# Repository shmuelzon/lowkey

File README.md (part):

# LowKey

A battery-powered smart lock controller for a motorised deadbolt, built on the
Nordic **nRF54L15** with the nRF Connect SDK.

It speaks **Matter over Thread** and a **custom BLE GATT service at the same
time**, on one Bluetooth controller. The two are not alternatives selected at
build time - they run concurrently, each with its own advertising set and its
own Bluetooth identity, so the lock stays controllable over BLE when the Thread
mesh or the Matter controller is down, and its BLE bonds survive Matter
commissioning and Matter factory resets.

| On the bench | Installed in a door |
| --- | --- |
|  |  |

## Features

- **Three distinct actions**, matching what a mortise deadbolt can actually do:
  lock, unbolt (retract the bolt, spring latch still holds the door), and open
  (retract the bolt *and* hold the latch back so the door can be pushed).
  These map to the Matter `LockDoor`, `UnboltDoor` and `UnlockDoor` commands.
- **Position tracked from the bolt, not from the motor.** The lock body's two
  magnetic end-stop sensors are monitored continuously, so operating the lock
  with a physical key updates the reported state exactly like a remote command
  does.
- **Jam detection** - the motor stops and the lock reports jammed, with a Matter
  `DoorLockAlarm` event, if an end-stop is not reached in time.
- **Door position sensor**, reported as a Matter `DoorStateChange`.
- **Battery monitoring** with a MAX17205 ModelGauge m5 fuel gauge, plus charger
  connected/complete status.
- **Firmware update** over both Bluetooth SMP (MCUmgr) and Matter OTA, sharing
  one MCUboot slot pair with LZMA-compressed images.
- **Per-device provisioning** - serial number, BLE pairing passkey, Matter
  discriminator and SPAKE2+ verifier in a dedicated flash partition that OTA
  never touches.
- **Task watchdog** with a channel per critical thread.

## Hardware

### Lock body

The mechanism is a **Rav Bariach RBM1**, a motorised mortise lock. The motor
unit and the magnetic sensors for the two bolt end-stops come built into the
body. The controller only has to drive the motor and read the sensors, all
through one 6-pin harness:

| Pin | Signal |
| --- | --- |
| 1 | 3.3 V (sensor supply) |
| 2 | GND |
| 3 | Unlocked end-stop |
| 4 | Locked end-stop |
| 5, 6 | Motor |

See [Adapting to a different lock body](#adapting-to-a-different-lock-body) if
yours is different.

<br clear="right">

### Electronics

One KiCad project holds three boards, panelised with mouse bites:

- **Main board**: the **Ezurio BL54L15** module (nRF54L15, with an MHF4
  connector for an external antenna, so there is no RF switch to manage),
  charger, regulator, fuel gauge, motor driver, and connectors for the
  battery, the lock harness, the door sensor and SWD.
- **UI board**: the two keys, the status LED and the USB-C charging port. It
  connects to the main board over an 8-way FFC.
- **Door sensor board**: a single Hall sensor with a 3-pin JST XH cable to
  the main board. It also carries an alternative footprint for a Coto RR123
  magnetoresistive sensor, which is not fitted.

Power comes from a 2S Li-ion pack, two 18650 or 21700 cells in series, on a
2-pin JST XH connector. See [Battery life](#battery-life) for what to expect
from each.

| Part | Role |
| --- | --- |
| Ezurio 453-00044R (BL54L15) | nRF54L15 module |
| TE 2344656-6 | External 2.4 GHz antenna |
| TI BQ25886 | 2S battery charger from USB-C, 1.03 A charge current (ITERM 103 mA) |
| TI TPS629203 | 3.3 V buck regulator |
| ADI MAX17205 | 2S fuel gauge, I²C `0x36`, 10 mΩ shunt |
| TI DRV8871 | H-bridge motor driver |
| Honeywell SL353LT | Door sensor, on its own board |

- [**Schematic (PDF)**](hardware/pcb/smart-lock.pdf)
- [KiCad project](hardware/pcb/) (KiCad 10). Custom 3D models are embedded
  in the board file, so the 3D viewer needs no extra libraries.

### Enclosures

| Controller | UI |
| --- | --- |
|  |  |
| [`controller.stl`](hardware/3d/controller.stl), from [`controller.scad`](hardware/3d/controller.scad) | [`ui.stl`](hardware/3d/ui.stl), from [`ui.scad`](hardware/3d/ui.scad) |

- **Controller**: a 42 × 42 × 13.8 mm box for the main board. It has openings
  for the lock harness, the battery lead and the UI cable, and closes with
  three M2 countersunk screws into heat-set inserts.
- **UI**: a Ø34 mm dome for the UI board, with lock and unlock icons embossed
  beside the two key caps. It closes with two M2 countersunk screws into
  heat-set inserts.

Both enclosures use 3.45 mm outer-diameter M2 inserts. Each STL holds every
part of its enclosure (base, lid and, for the UI, the key caps) as separate
bodies; split them into objects in your slicer. The `show_*` variables at the
top of each `.scad` export a single part.

### Regenerating the outputs

The PDF, the renders and the STLs are committed so they can be viewed on
GitHub. After changing a source, regenerate them with:

```sh
make -C hardware          # everything
make -C hardware pcb      # schematic PDF and board render (KiCad 10)
make -C hardware 3d       # STLs and enclosure renders (OpenSCAD)
```

The Makefile finds `kicad-cli`, `openscad` and ImageMagick's `magick` in
`PATH`, in their usual macOS locations, and under `C:\Program Files` from WSL or
Git Bash. Point it at a tool anywhere else with
`make KICAD_CLI=... OPENSCAD=... MAGICK=...`. ImageMagick is optional: it gives
the renders a transparent background and trims them to the model.

OpenSCAD must be a development snapshot with the Manifold backend. The 2021.01
release only has CGAL, which rejects the imported PCB meshes and silently drops
their cutouts, so the Makefile refuses to use it.

## Repository layout

```
boards/shmuelzon/lowkey/   Board definition (revisions A and B) and its DTS bindings
src/                       Application
  ├─ lock_manager.c        Motor drive and the bolt/latch state machine
  ├─ door_monitor.c        Door position sensor
  ├─ battery_manager.c     MAX17205 fuel gauge and charger status
  ├─ ui.c                  Keys and status LED
  ├─ gpio_input.c          Interrupt-driven GPIO inputs, optionally debounced
  ├─ watchdog.c            Task watchdog
  ├─ radio.c               Fans the radio API out to the backends below
  ├─ ble/                  Custom GATT services (CONFIG_LOCK_RADIO_BLE)
  └─ matter/               Clusters and ZAP data model (CONFIG_LOCK_RADIO_MATTER)
scripts/                   Factory-data generation, device label, Intel HEX padding
sysbuild/mcuboot/          MCUboot configuration
pm_static.yml              Flash partition layout
hardware/                  Makefile that regenerates the outputs below
  ├─ pcb/                  KiCad project, schematic PDF and board render
  └─ 3d/                   OpenSCAD enclosures, STLs and renders
docs/                      README media
```

## Getting started

Built against **nRF Connect SDK v3.2.4**.

```sh
# Toolchain and SDK
curl -o ~/bin/nrfutil "https://files.nordicsemi.com/ui/api/v1/download?repoKey=swtools&path=external/nrfutil/executables/x86_64-unknown-linux-gnu/nrfutil&isNativeBrowsing=false"
chmod +x ~/bin/nrfutil
nrfutil install sdk-manager toolchain-manager
nrfutil sdk-manager install v3.2.4
cd ~/ncs/v3.2.4 && west update

# Per-shell environment (needed for west build and west zap-generate)
SDK_VERSION=v3.2.4
source ~/ncs/$SDK_VERSION/zephyr/zephyr-env.sh
eval $(nrfutil toolchain-manager env --ncs-version $SDK_VERSION --as-script)

# Python packages used by the provisioning script
pip install cbor2 intelhex jsonschema pillow pyyaml qrcode
```

## Building

The board has two PCB revisions, selected with the `@` suffix. They differ only
in the motor driver: **rev A** (DRV8837) has an `nSLEEP` enable pin, **rev B**
(DRV8871) sleeps on its own and omits it.

```sh
# Product build: both radios, release
west build --pristine -b lowkey@B/nrf54l15/cpuapp -- -DBOARD_ROOT="$PWD"

# Debug: RTT console and logging
west build --pristine -b lowkey@B/nrf54l15/cpuapp -- -DBOARD_ROOT="$PWD" \
    -DEXTRA_CONF_FILE="overlay-debug.conf"

# One radio only
west build --pristine -b lowkey@B/nrf54l15/cpuapp -d build-ble -- \
    -DBOARD_ROOT="$PWD" -DCONFIG_LOCK_RADIO_MATTER=n -DSB_CONFIG_MATTER=n
west build --pristine -b lowkey@B/nrf54l15/cpuapp -d build-matter -- \
    -DBOARD_ROOT="$PWD" -DCONFIG_LOCK_RADIO_BLE=n
```

Both radios are on by default. There are no `prj_*.conf` protocol fragments -
`CONFIG_LOCK_RADIO_BLE` and `CONFIG_LOCK_RADIO_MATTER` in the project `Kconfig`
carry all protocol-specific configuration, so a build is described by the board
plus those two switches.

Approximate image sizes (of the 810 KiB application slot):

| Build | Flash | RAM |
| --- | --- | --- |
| Both radios | 78 % | 79 % |
| Both radios, debug | 90 % | 80 % |
| Matter only | 72 % | 68 % |
| BLE only | 24 % | 28 % |

Two things that will bite you:

- **Use `-DEXTRA_CONF_FILE`, not `-DOVERLAY_CONFIG`.** Under sysbuild the latter
  is applied to *every* image, including MCUboot, where it breaks image signing
  with a confusing `@PM_MCUBOOT_PRIMARY_SIZE@ is not a valid integer`.
- **`-DSB_CONFIG_MATTER=n` is separate from `-DCONFIG_LOCK_RADIO_MATTER=n`.**
  Sysbuild's Kconfig cannot see the application's, so a Matter-less build still
  emits a `matter.ota` artifact unless you pass both.

### Changing the Matter data model

The files under `src/matter/zap-generated/` are generated from
`src/matter/lock.zap`:

```sh
west zap-gui        # or edit the JSON directly
west zap-generate
```

If you **add or remove a cluster**, force a CMake reconfigure before rebuilding
(`touch CMakeLists.txt`, or build `--pristine`). Cluster-to-source selection
happens at configure time only, so an incremental build fails at link with
something like `undefined reference to MatterPowerSourcePluginServerInitCallback`.

## Flashing

A build produces `build/merged.hex` (MCUboot + signed application) for SWD,
`build/dfu_application.zip` for MCUmgr, and `build/matter.ota` for Matter OTA.

```sh
./scripts/pad_hex.py build/merged.hex
west flash
```

> ### Pad the HEX file first
>
> `scripts/pad_hex.py` pads the last data record of an Intel HEX file to 16
> bytes with `0xFF`. This works around an OpenOCD nRF5 driver issue where the
> RRAMC write buffer is not flushed for a trailing partial block, which
> **silently corrupts the ED25519 signature** at the end of the MCUboot image -
> the device then refuses to boot for no visible reason.
>
> This affects on-board debuggers driven through OpenOCD, including the one on
> the Seeed XIAO nRF54L15. Run it before every flash, on `merged.hex` and on
> `factory_data.hex` alike. It is idempotent.

## Provisioning

Every device needs its own factory data: a serial number, a BLE pairing
passkey, and (for Matter) a discriminator and SPAKE2+ verifier. These live in a
4 KiB `factory_data` partition that firmware updates never overwrite.

```sh
python3 scripts/generate_factory_data.py -o factory_data
./scripts/pad_hex.py factory_data.hex
nrfutil device program --firmware factory_data.hex --core application \
    --options chip_erase_mode=ERASE_RANGES_TOUCHED_BY_FIRMWARE,reset=RESET_SYSTEM
```

Every argument has a default and the per-device secrets are drawn randomly when
not given, so the command above is the whole flow for a development unit. It
writes five files:

| File | Contents |
| --- | --- |
| `factory_data.hex` | The partition image, at the offset and size read from `pm_static.yml` |
| `factory_data.json` | Every generated value **except** the Matter passcode |
| `factory_data.txt` | Matter manual pairing code and QR payload |
| `factory_data.png` | The same QR code as an image |
| `factory_data.sticker.png` | A printable device label: Matter QR and pairing code, BLE name, serial number and BLE passkey |

Archive the `.json` and `.txt` per device - together they are the only record.
Use `--no-matter` for a BLE-only build, and `--help` for the full set of
overrides (`--sn`, `--ble_passkey`, `--passcode`, `--discriminator`,
`--battery_capacity_mah`, the DAC/PAI certificate paths, `--sticker-size`,
`--no-sticker`, …). To reprint the label for a unit provisioned earlier, run
`python3 scripts/generate_sticker.py factory_data`.

*An example label. Its codes were randomly generated and belong to no device.*

> ### The onboarding codes printed at boot are wrong
>
> The Matter passcode is deliberately **not** stored on the device - only the
> one-way SPAKE2+ verifier is, so reading out the flash does not reveal it. The
> firmware therefore cannot rebuild its own onboarding payload and falls back to
> Matter's example passcode, making the `Manual pairing code` and `SetupQRCode`
> lines in its boot log useless:
>
> ```
> [DL]  Setup Pin Code (0 for UNKNOWN/ERROR): 0
> [SVR]*** Using default EXAMPLE passcode 20202021 ***
> ```
>
> **Commission with the codes in `factory_data.txt`.** Pass `--include-passcode`
> if you would rather store the passcode and trust the boot log, at the cost of
> it being readable out of flash.

### Before shipping anything

The stock configuration is a development configuration:

- **Attestation certificates** default to the Matter SDK's *test* DAC/PAI for
  test VID/PID `0xFFF1`/`0x8000`. Production devices need certificates from a
  real PAA. The script warns if you change the VID/PID without supplying them.
- **Images are signed with MCUboot's public development key**, so anyone can
  produce an image this bootloader accepts. Generate your own and point the
  build at it - this cannot be changed after units ship, because MCUboot is the
  immutable first-stage bootloader:
  ```sh
  imgtool keygen -k prod-ed25519.pem -t ed25519
  west build ... -- -DSB_CONFIG_BOOT_SIGNATURE_KEY_FILE="$PWD/prod-ed25519.pem"
  ```
  On nRF54L15, `SB_CONFIG_BOOT_SIGNATURE_USING_KMU` can hold the public key in
  hardware instead of bootloader flash.

## Using the lock

### Keys and LED

The key layout is chosen at build time from devicetree, by whether a `key1`
alias exists:

| | Short press | Long press |
| --- | --- | --- |
| **key0** | Lock | Factory reset (10 s) |
| **key1** | Unbolt | Open for commissioning / pairing (1.5 s) |

On a board with only `key0`, a short press opens the discovery window and the
long press is still factory reset - both are mandatory in every layout, and the
build fails if either is unassigned. Factory reset sits on the *lock* key
deliberately: the key someone leans on when the door will not open is the unlock
one, and ten seconds of that should not wipe the fabric.

| LED | Meaning |
| --- | --- |
| Fast blink (100 ms) | Factory reset fires in 3 seconds - release to abort |
| Slow blink (500 ms) | Discoverable, identifying, or charging |
| Solid | Charge complete |
| Off | Idle |

One press of the discovery key opens an onboarding window on **both** radios and
lets your app pick; the first to complete closes the other. To pair a BLE client
*and* commission to Matter, press it twice, once per path.

### Matter

Endpoint 1 exposes **Door Lock** (with the `Unbolting` and `DoorPositionSensor`
features), **Power Source**, **Identify** and **ICD Management**. There is no
PIN/RFID/user support - the lock has no keypad, and those cluster features are
deliberately absent from the data model rather than stubbed.

The device is a Thread **sleepy end device**. Inbound latency is bounded by the
ICD poll interval (500 ms idle); outbound reporting of bolt and door changes is
immediate.

### BLE

| Service / characteristic | UUID | Properties |
| --- | --- | --- |
| Lock service | `1e3557d1-0001-5887-a357-c9acbd789b14` | |
| ├ Lock status | `1e3557d1-0002-5887-a357-c9acbd789b14` | Read, Notify (encrypted) |
| └ Lock request | `1e3557d1-0003-5887-a357-c9acbd789b14` | Write (authenticated) |
| Door service | `1e3557d1-0010-5887-a357-c9acbd789b14` | |
| └ Door state | `1e3557d1-0011-5887-a357-c9acbd789b14` | Read, Notify (encrypted) |
| Battery service | `0x180F` | Standard |
| Device Information | `0x180A` | Populated from factory data |

Lock status values: `0` locked, `1` locking, `2` unlocked, `3` unlocking,
`4` jammed, `5` unlatched, `6` unknown. Lock request values: `0` lock,
`1` unbolt, `2` open.

The lock advertises as `LowKey-XXXX`, where `XXXX` is the last four characters
of the serial number, so the name on the label matches without reading anything
off the device.

## Porting to another board

The application depends only on the devicetree contract below - no board-specific
code. Everything is reached through aliases except three node labels.

### Required aliases

| Alias | Direction | Expected wiring |
| --- | --- | --- |
| `led0` | Output | Status LED |
| `key0` | Input | Push button, active low with pull-up |
| `key1` | Input | Second button. **Optional** - its presence changes the key layout |
| `lock-sensor` | Input | Active when the bolt is fully extended |
| `unlock-sensor` | Input | Active when the bolt is fully retracted |
| `door-sensor` | Input | Active when the door is closed |
| `chg-power-good` | Input | Active when input power is present |
| `chg-stat` | Input | Active while charging; inactive means complete |

Every input is configured for **both-edge interrupts**, so all of them must be
on interrupt-capable pins. On the nRF54L15 that means P0 or P1 - **P2 has no
GPIOTE peripheral**.

### Required node labels

| Label | Notes |
| --- | --- |
| `motor_driver` | `compatible = "lowkey,motor-driver"`; `in1-gpios` and `in2-gpios` required, `nsleep-gpios` optional |
| `max17205` | `compatible = "maxim,max17205"`, `reg = <0x36>`, `sense-resistor-micro-ohms`, `charge-term-current-microamp` |
| `wdt31` | Referenced by label, not by the `watchdog0` alias, and must be `status = "okay"` |

Plus a `factory_data` partition, supplied by Partition Manager from
`pm_static.yml`.

### Board-level requirements

- **`&cpuapp_rram { reg = <0x0 DT_SIZE_K(1524)>; }` in every image**, including
  MCUboot (`sysbuild/mcuboot/app.overlay`). `pm_static.yml` spans the full
  1524 KiB by reclaiming the unused FLPR coprocessor's RRAM; miss this in any
  one image and the layout overflows `flash_primary` and the build fails.
- **`&uicr { nfct-pins-as-gpios; }`** if you reuse P1.02/P1.03. These power up in
  NFC mode, and the NFCT pad network holds them low, overriding the GPIO
  pull-ups - the keys read stuck-low. Disabling the `nfct` node is *not* enough.
- **Disable `uart21` in MCUboot** on any board that enables it. If the UARTE
  driver initialises during MCUboot, its pins latch as UART-TX-idle-high and
  that hardware state survives into the application, overriding GPIO output.
- Keep application RAM low if you care about idle current: `power_down_unused_ram()`
  powers down whole 32 KiB SRAM sections above the image, so every 32 KiB the
  image gives back is one more section switched off.

### Tunables

All in the project `Kconfig`, prefixed `CONFIG_LOCK_`:

| Symbol | Default | Purpose |
| --- | --- | --- |
| `MOTOR_TIMEOUT_MS` | 3000 | End-stop not reached in this time ⇒ jammed |
| `MOTOR_BRAKE_US` | 2000 | Dynamic braking before coasting and before reversing |
| `BOLT_SEATING_MS` | 100 | Extra drive after the lock end-stop, to seat the bolt |
| `UNBOLT_SEATING_MS` | 0 | Extra drive after the unlock end-stop |
| `LATCH_RELEASE_MS` | 500 | Extra drive on an open, to hold the latch back |
| `BATTERY_POLL_INTERVAL_S` | 60 | Fuel gauge polling |
| `BUTTON_DEBOUNCE_MS` | 30 | Mechanical key debounce |
| `WATCHDOG_TIMEOUT_MS` | 30000 | Task watchdog, per channel |
| `WATCHDOG_FEED_MS` | 5000 | Feed interval |
| `DISCOVERY_TIMEOUT_S` | 180 / 60 | Onboarding window (180 with Matter) |
| `DISCOVERY_PRESS_MS` | 1500 | Hold time for discovery |
| `FACTORY_RESET_PRESS_MS` | 10000 | Hold time for factory reset |
| `BLE_TX_POWER_DBM` | 7 | Applied at runtime over vendor HCI |

## Adapting to a different lock body

The mechanism needs, at minimum:

- **Two motor pins** into an H-bridge (`in1-gpios`, `in2-gpios`), plus an
  optional enable pin (`nsleep-gpios`) if the driver has one.
- **Two end-stop sensors** telling the firmware when the bolt has reached each
  extreme.
- **One door sensor** (optional in practice - omit the Matter
  `DoorPositionSensor` feature from `lock.zap` if you have none).

The H-bridge is driven as:

| IN1 | IN2 | Effect |
| --- | --- | --- |
| 0 | 0 | Coast (idle) |
| 0 | 1 | Drive toward locked |
| 1 | 0 | Drive toward unlocked |
| 1 | 1 | Brake |

Swap `in1-gpios` and `in2-gpios` if your motor runs the wrong way.

Sensors are expected to be **solid-state, active-low, with no pull-up** - Hall
sensors with a push-pull output stage, where a pull-up would only waste current.
They are deliberately **not debounced**: they do not bounce, and any delay here
lands between the end-stop firing and the motor stopping, adding bolt travel.
Only the mechanical keys are debounced. If you use reed switches or another
bouncing sensor, pass a non-zero debounce to `gpio_input_init()` in
`lock_manager.c` and `door_monitor.c`.

Timing notes for a different mechanism:

- `LATCH_RELEASE_MS` **is** the window during which the door can be pushed open.
  The latch is spring-loaded and returns the instant the motor releases the cam,
  so this is a usability number, not just a mechanical one.
- `UNBOLT_SEATING_MS` defaults to 0 because on this lock the unbolt travel heads
  *toward* the latch, so any extra drive starts releasing it. If your mechanism
  is different, this is where extra retraction goes.
- A Matter build **refuses** `LATCH_RELEASE_MS=0` (a `BUILD_ASSERT`), because
  `lock.zap` advertises the Door Lock `Unbolting` feature, which promises a
  controller that `UnlockDoor` pulls the latch. Clear that feature bit from the
  FeatureMap if your lock cannot.

## Power

The design targets a multi-year battery life on a 2S pack. What the firmware
does for it:

- `vregmain` in DCDC mode, and unused SRAM sections powered down at boot.
- Thread MTD/sleepy end device, with the ICD intervals retuned - the NCS
  defaults are self-defeating, because the fast poll interval is longer than the
  active-mode duration, so the fast interval is unreachable and every round trip
  of a multi-message exchange pays the full idle interval.
- BLE advertising slows to a ~1 s interval once bonded.
- The motor driver sleeps between operations, and the fuel gauge is polled once
  a minute plus once after each completed operation.
- Runtime device PM, so the I²C peripheral is suspended between transfers.

### Battery life

Measured draw:

| State | Current |
| --- | --- |
| Idle | 70 µA |
| Motor running | 200 mA, for about 1 s per lock or unlock |

At around 40 lock/unlock cycles a day, a pack of two 3000 mAh 18650 cells in
series is expected to last about 1.3 years, and two 5000 mAh 21700 cells about
2.2 years.

## Known limitations

- **The onboarding codes in the boot log are wrong** unless you provision with
  `--include-passcode`. See
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
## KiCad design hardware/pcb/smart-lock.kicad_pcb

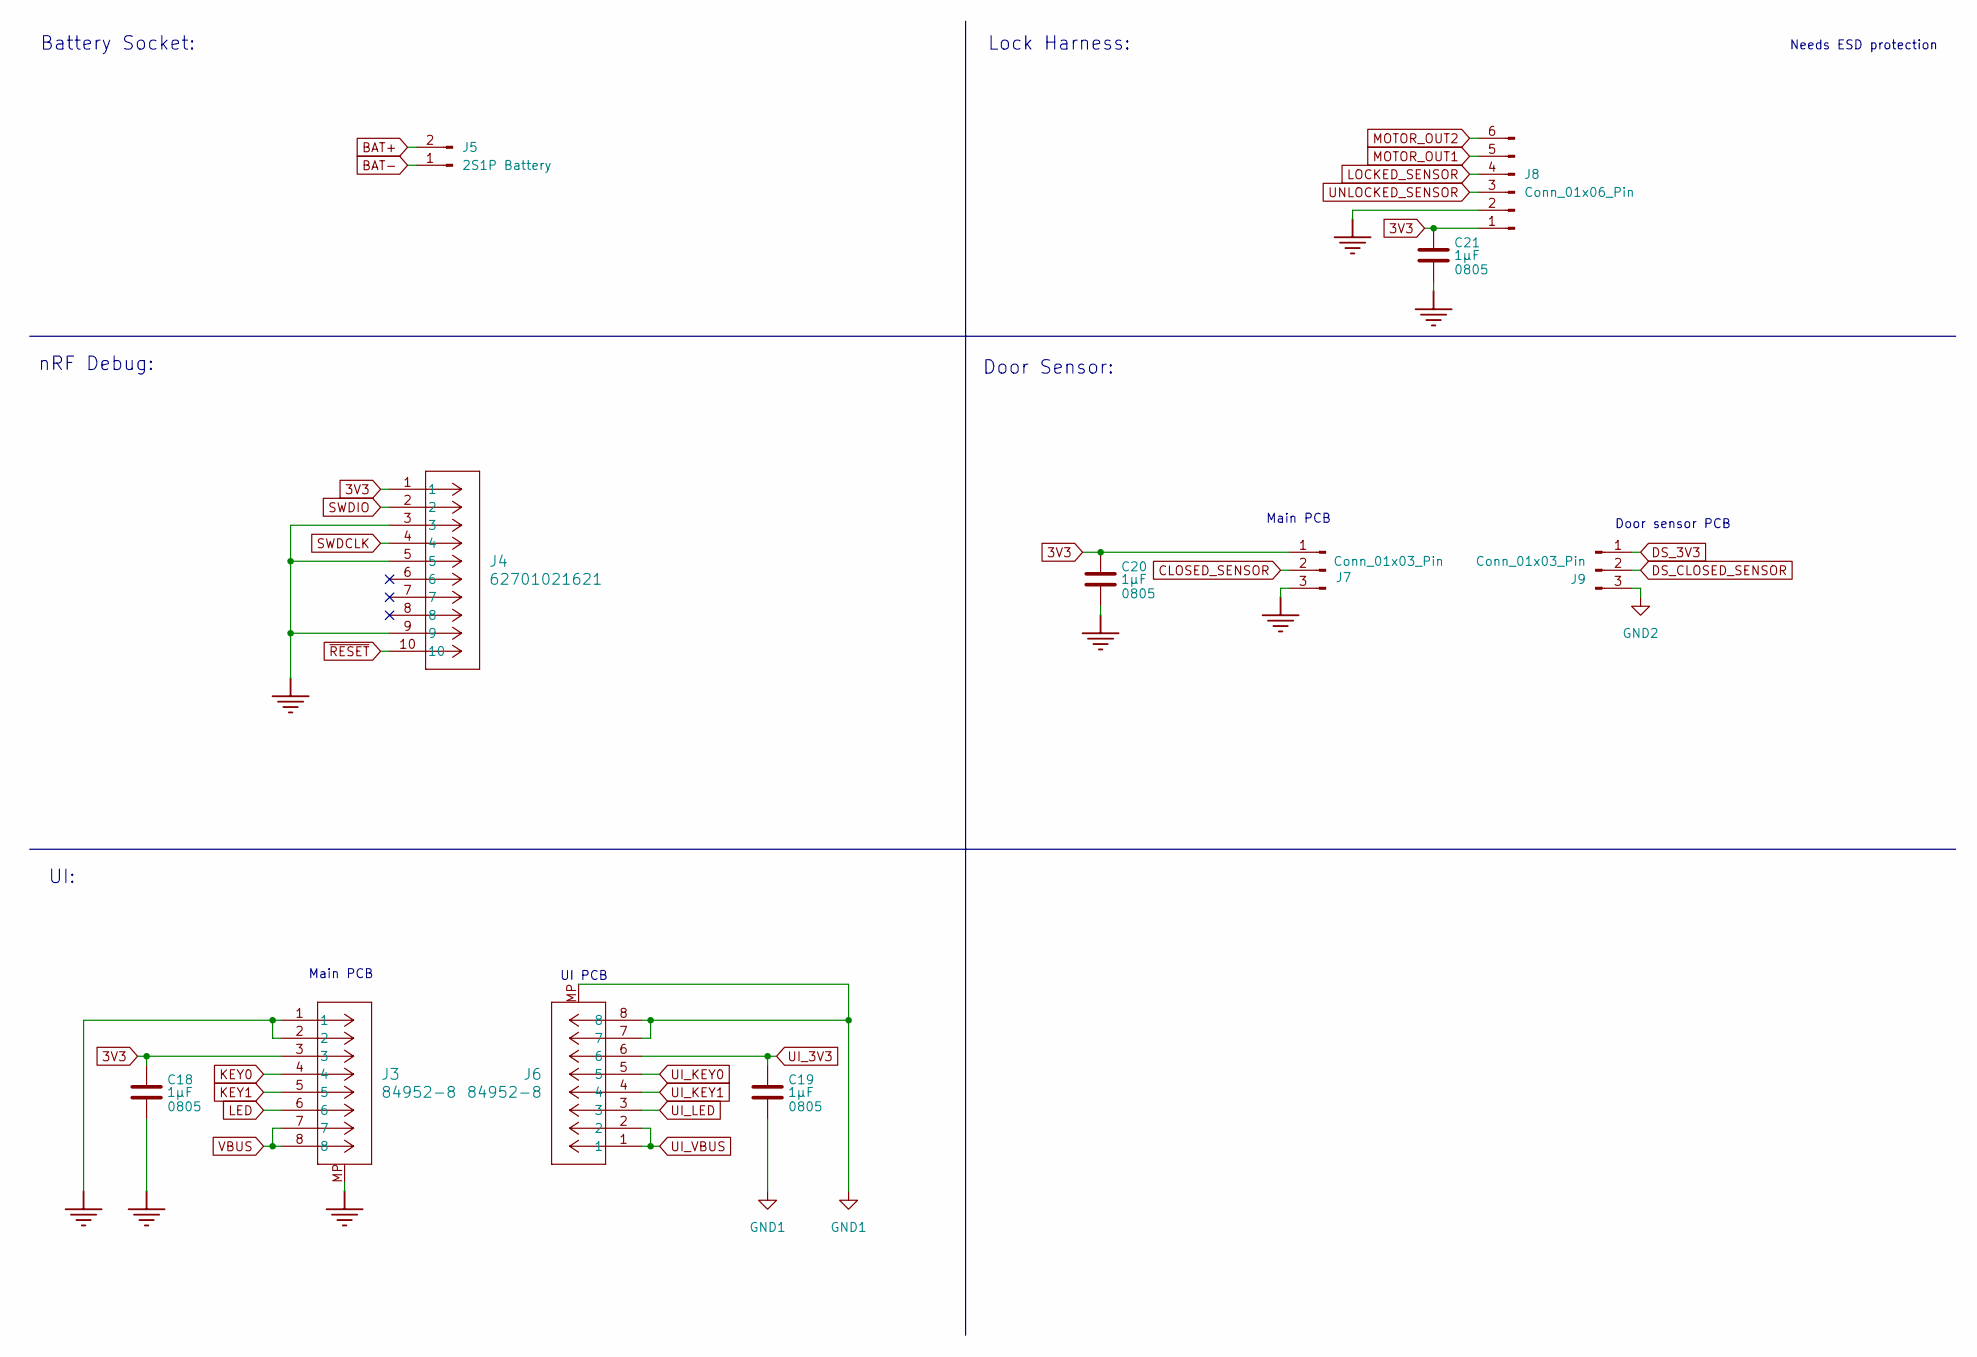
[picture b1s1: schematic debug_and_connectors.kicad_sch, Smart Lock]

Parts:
C18, C19, C20, C21: 1µF; C_0805_2012Metric; Voltage 10V; MANUFACTURER PART NUMBER GRM21BR71A105KA01K
J3, J6: 84952-8; CON8_SMT-RA_FCC-FPC2; MANUFACTURER PART NUMBER 84952-8
J4: 62701021621; CONN_62701021621_WRE; MANUFACTURER PART NUMBER 62701021621
J5: 2S1P Battery; JST_XH_S2B-XH-A_1x02_P2.50mm_Horizontal; MANUFACTURER PART NUMBER S2B-XH-A(LF)(SN)
J7: Conn_01x03_Pin; JST_XH_S3B-XH-A_1x03_P2.50mm_Horizontal; MANUFACTURER PART NUMBER S3B-XH-A(LF)(SN)
J8: Conn_01x06_Pin; JST_XH_S6B-XH-A_1x06_P2.50mm_Horizontal; MANUFACTURER PART NUMBER S6B-XH-A(LF)(SN)
J9: Conn_01x03_Pin; JST_XH_B3B-XH-A_1x03_P2.50mm_Vertical; MANUFACTURER PART NUMBER B3B-XH-A(LF)(SN)

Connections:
3V3: C18.1, C20.1, C21.1, J3.3, J4.1, J7.1, J8.1; also elsewhere on the board
BAT+: J5.2; also elsewhere on the board
BAT-: J5.1; also elsewhere on the board
CLOSED_SENSOR: J7.2; also elsewhere on the board
DS_3V3: J9.1; also elsewhere on the board
DS_CLOSED_SENSOR: J9.2; also elsewhere on the board
GND: C18.2, C20.2, C21.2, J3.1, J3.2, J3.MP, J4.3, J4.5, J4.9, J7.3, J8.2; also elsewhere on the board
GND1: C19.2, J6.7, J6.8, J6.MP; also elsewhere on the board
GND2: J9.3; also elsewhere on the board
KEY0: J3.4; also elsewhere on the board
KEY1: J3.5; also elsewhere on the board
LED: J3.6; also elsewhere on the board
LOCKED_SENSOR: J8.4; also elsewhere on the board
MOTOR_OUT1: J8.5; also elsewhere on the board
MOTOR_OUT2: J8.6; also elsewhere on the board
SWDCLK: J4.4; also elsewhere on the board
SWDIO: J4.2; also elsewhere on the board
UI_3V3: C19.1, J6.6; also elsewhere on the board
UI_KEY0: J6.5; also elsewhere on the board
UI_KEY1: J6.4; also elsewhere on the board
UI_LED: J6.3; also elsewhere on the board
UI_VBUS: J6.1, J6.2; also elsewhere on the board
UNLOCKED_SENSOR: J8.3; also elsewhere on the board
VBUS: J3.7, J3.8; also elsewhere on the board
~RESET: J4.10; also elsewhere on the board

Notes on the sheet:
Needs ESD protection
UI:
Main PCB
nRF Debug:
UI PCB
Battery Socket:
Door sensor PCB
Door Sensor:
Lock Harness:

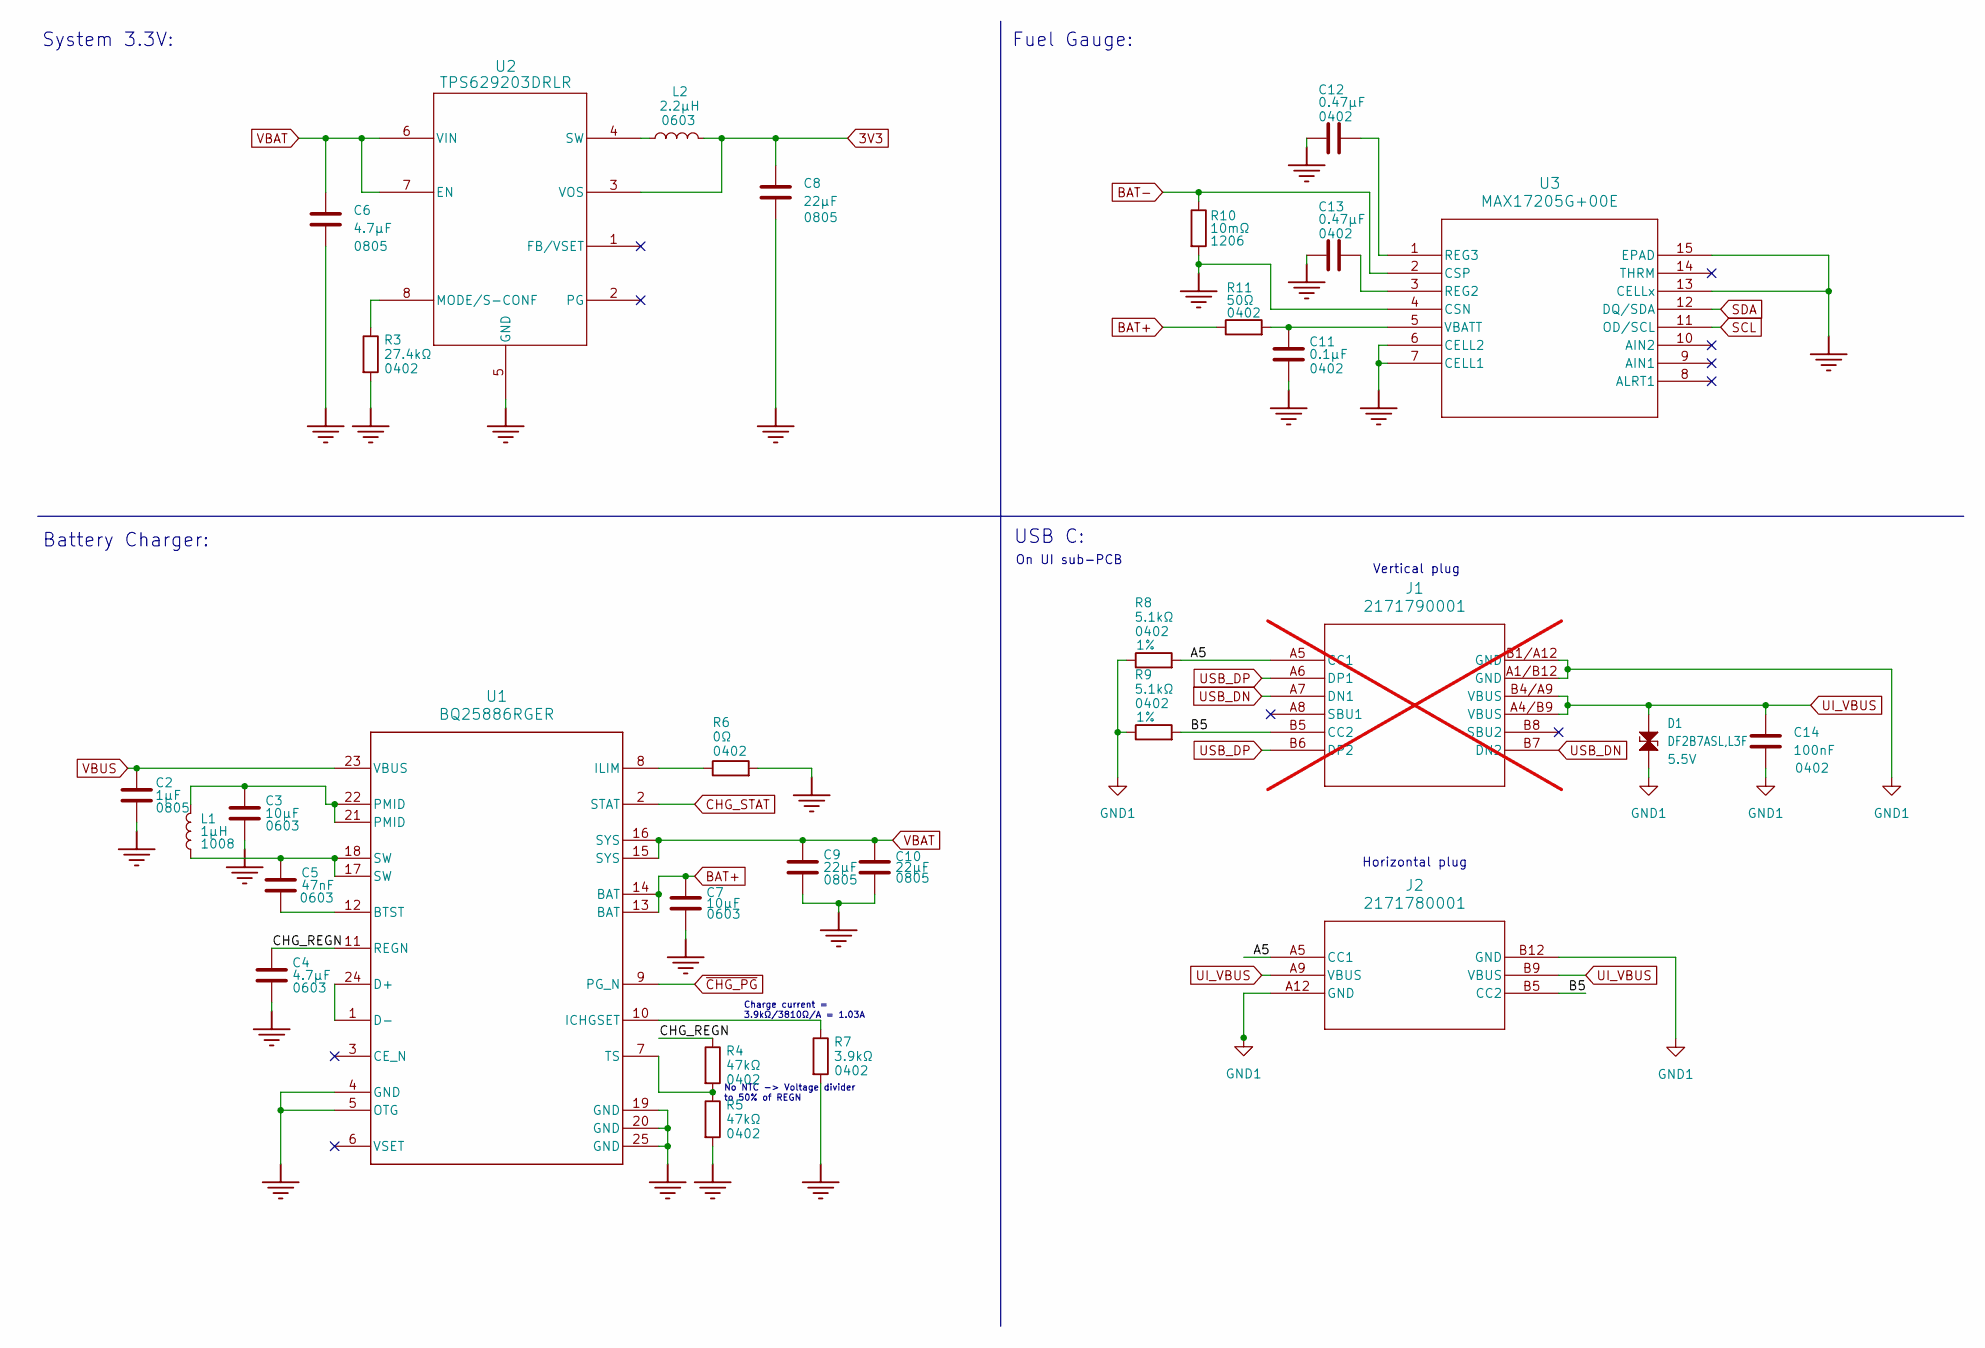
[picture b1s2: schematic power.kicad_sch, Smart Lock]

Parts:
C2: 1µF; C_0805_2012Metric; Voltage 10V; MANUFACTURER PART NUMBER GRM21BR71A105KA01K
C3, C7: 10µF; C_0603_1608Metric; Voltage 16V; MANUFACTURER PART NUMBER GRM188R61C106MA73D
C4: 4.7µF; C_0603_1608Metric; Voltage 16V; MANUFACTURER PART NUMBER GRT188C71C475KE13D
C5: 47nF; C_0603_1608Metric; Voltage 25V; MANUFACTURER PART NUMBER GCM188R71E473KA37D
C6: 4.7µF; C_0805_2012Metric; Voltage 16V; MANUFACTURER PART NUMBER GRM21BR71C475KE51L
C8, C9, C10: 22µF; C_0805_2012Metric; Voltage 25V; MANUFACTURER PART NUMBER GRM21BR61E226ME44L
C11: 0.1µF; C_0402_1005Metric; Voltage 25V; MANUFACTURER PART NUMBER GRM155R71E104KE14J
C12, C13: 0.47µF; C_0402_1005Metric; Voltage 6.3V; MANUFACTURER PART NUMBER GRM155R60J474KE19D
C14: 100nF; C_0402_1005Metric; Voltage 16V; MANUFACTURER PART NUMBER GRM155R71C104KA88D
D1: DF2B7ASL,L3F; D_0201_0603Metric; Voltage 5.5V; MANUFACTURER PART NUMBER DF2B7ASL,L3F
J1: 2171790001; 2171790001_MOL; MANUFACTURER PART NUMBER 2171790001; not fitted
J2: 2171780001; CONN_2171780001_MOL; MANUFACTURER PART NUMBER 2171780001
L1: 1µH; L_1008_2520Metric; MANUFACTURER PART NUMBER DFE252012F-1R0M=P2
L2: 2.2µH; INDC1608X06L; MANUFACTURER PART NUMBER MLZ1608A2R2WT000
R3: 27.4kΩ; R_0402_1005Metric; MANUFACTURER PART NUMBER RC0402FR-1327K4L
R4, R5: 47kΩ; R_0402_1005Metric; MANUFACTURER PART NUMBER RC0402FR-0747KL
R6: 0Ω; R_0402_1005Metric; MANUFACTURER PART NUMBER RC0402JR-070RL
R7: 3.9kΩ; R_0402_1005Metric; MANUFACTURER PART NUMBER RC0402FR-073K9L
R8, R9: 5.1kΩ; R_0402_1005Metric; Tolerance 1%; MANUFACTURER PART NUMBER RC0402FR-075K1L
R10: 10mΩ; R_1206_3216Metric; MANUFACTURER PART NUMBER PE1206DRM7W0R01L
R11: 50Ω; R_0402_1005Metric; MANUFACTURER PART NUMBER RC0402JR-0750RL
U1: BQ25886RGER; RGE0024H_NV; MANUFACTURER PART NUMBER BQ25886RGER
U2: TPS629203DRLR; SOT-5x3_DRL0008A_TEX-L; MANUFACTURER PART NUMBER TPS629203DRLR
U3: MAX17205G+00E; MAX17205G; MANUFACTURER PART NUMBER MAX17205G+00E

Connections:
3V3: C8.1, L2.2, U2.3 (VOS); also elsewhere on the board
/Power/A5: J1.A5 (CC1), J2.A5 (CC1), R8.2
/Power/B5: J1.B5 (CC2), J2.B5 (CC2), R9.2
/Power/CHG_REGN: C4.1, R4.1, U1.11 (REGN)
BAT+: C7.1, R11.1, U1.13 (BAT), U1.14 (BAT); also elsewhere on the board
BAT-: R10.1, U3.2 (CSP); also elsewhere on the board
CHG_STAT: U1.2 (STAT); also elsewhere on the board
GND: C2.2, C3.2, C4.2, C6.2, C7.2, C8.2, C9.2, C10.2, C11.2, C12.1, C13.1, R3.2, R5.2, R6.2, R7.2, R10.2, U1.4 (GND), U1.5 (OTG), U1.19 (GND), U1.20 (GND), U1.25 (GND), U2.5 (GND), U3.4 (CSN), U3.6 (CELL2), U3.7 (CELL1), U3.13 (CELLx), U3.15 (EPAD); also elsewhere on the board
GND1: C14.2, D1.1, J1.A1/B12 (GND), J1.B1/A12 (GND), J2.A12 (GND), J2.B12 (GND), R8.1, R9.1; also elsewhere on the board
unnamed: C3.1, L1.2, U1.21 (PMID), U1.22 (PMID)
unnamed: C5.1, L1.1, U1.17 (SW), U1.18 (SW)
unnamed: C5.2, U1.12 (BTST)
unnamed: U1.1 (D-), U1.24 (D+)
unnamed: R7.1, U1.10 (ICHGSET)
unnamed: R6.1, U1.8 (ILIM)
unnamed: R4.2, R5.1, U1.7 (TS)
unnamed: R3.1, U2.8 (MODE/S-CONF)
unnamed: L2.1, U2.4 (SW)
unnamed: C13.2, U3.3 (REG2)
unnamed: C12.2, U3.1 (REG3)
unnamed: C11.1, R11.2, U3.5 (VBATT)
SCL: U3.11 (OD/SCL); also elsewhere on the board
SDA: U3.12 (DQ/SDA); also elsewhere on the board
UI_VBUS: C14.1, D1.2, J1.A4/B9 (VBUS), J1.B4/A9 (VBUS), J2.A9 (VBUS), J2.B9 (VBUS); also elsewhere on the board
USB_DN: J1.A7 (DN1), J1.B7 (DN2)
USB_DP: J1.A6 (DP1), J1.B6 (DP2)
VBAT: C6.1, C9.1, C10.1, U1.15 (SYS), U1.16 (SYS), U2.6 (VIN), U2.7 (EN); also elsewhere on the board
VBUS: C2.1, U1.23 (VBUS); also elsewhere on the board
~CHG_PG: U1.9 (PG_N); also elsewhere on the board

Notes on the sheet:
Battery Charger:
Vertical plug
No NTC -> Voltage divider to 50% of REGN
On UI sub-PCB
USB C:
Horizontal plug
System 3.3V:
Fuel Gauge:
Charge current = 3.9kΩ/3810Ω/A = 1.03A

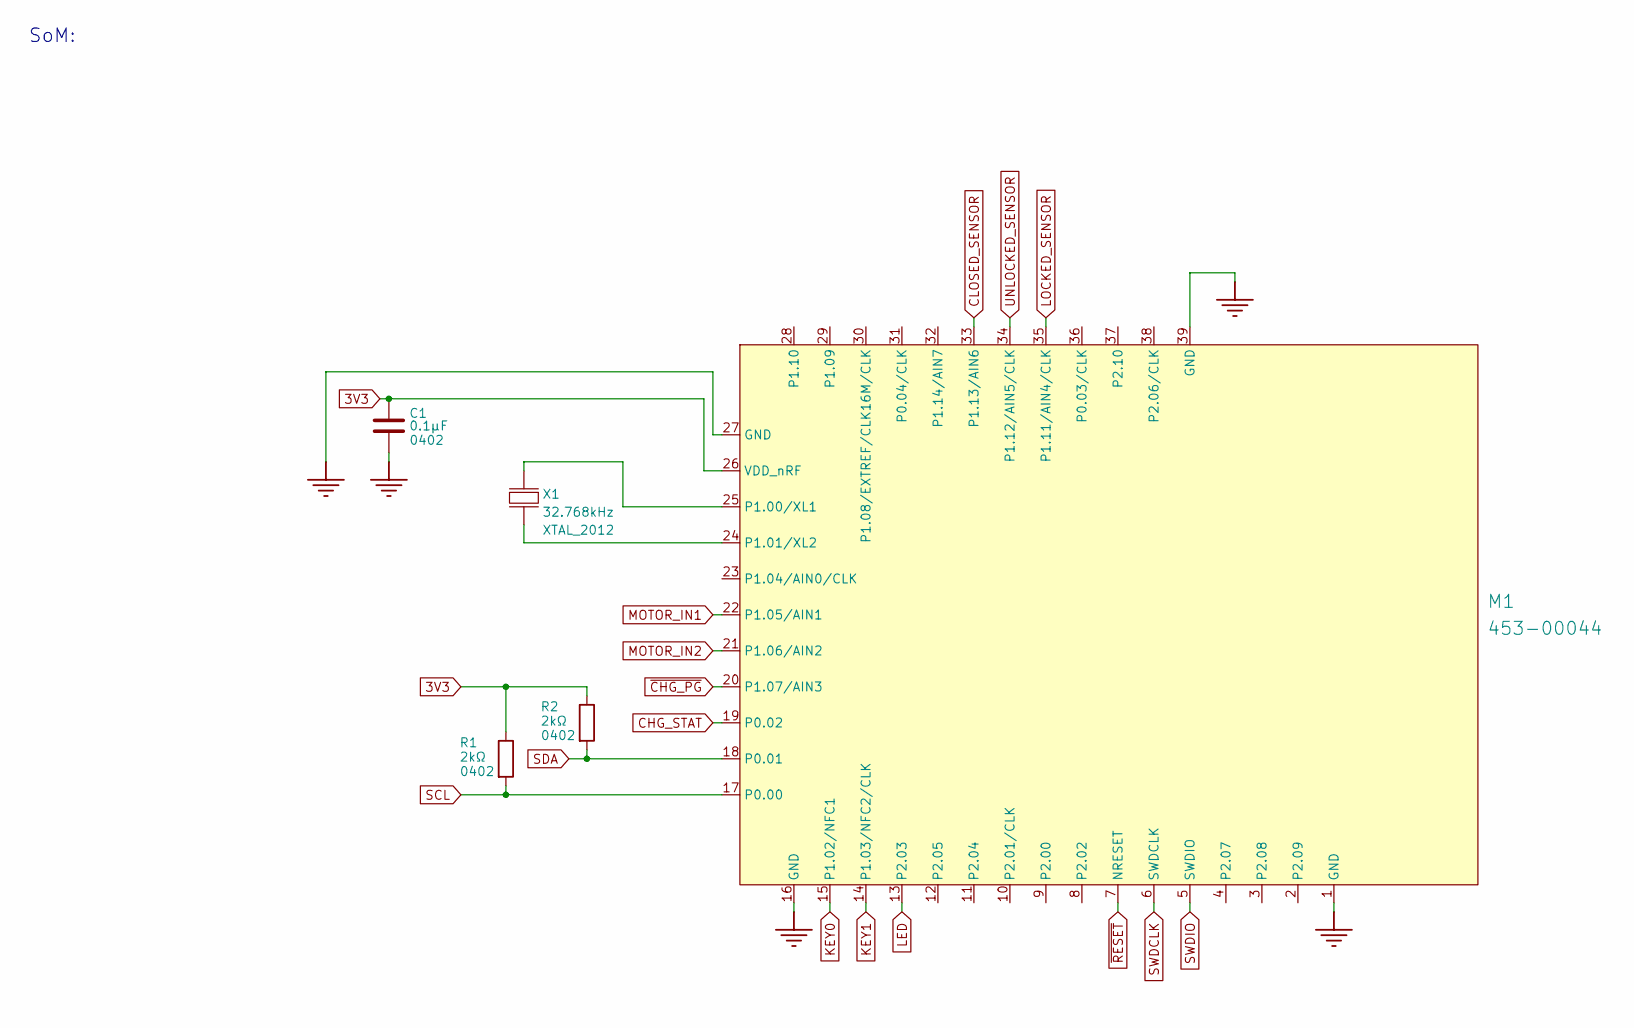
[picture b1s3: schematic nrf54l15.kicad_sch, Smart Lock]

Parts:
C1: 0.1µF; C_0402_1005Metric; Voltage 25V; MANUFACTURER PART NUMBER GRM155R71E104KE14J
M1: 453-00044; MANUFACTURER PART NUMBER 453-00044R
R1, R2: 2kΩ; R_0402_1005Metric; MANUFACTURER PART NUMBER RC0402FR-072KL
X1: 32.768kHz; XTAL_2012; MANUFACTURER PART NUMBER 9HT11-32.768KDZC-T

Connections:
3V3: C1.1, M1.26 (VDD_nRF), R1.1, R2.1; also elsewhere on the board
CHG_STAT: M1.19 (P0.02); also elsewhere on the board
CLOSED_SENSOR: M1.33 (P1.13/AIN6); also elsewhere on the board
GND: C1.2, M1.1 (GND), M1.16 (GND), M1.27 (GND), M1.39 (GND); also elsewhere on the board
KEY0: M1.15 (P1.02/NFC1); also elsewhere on the board
KEY1: M1.14 (P1.03/NFC2/CLK); also elsewhere on the board
LED: M1.13 (P2.03); also elsewhere on the board
LOCKED_SENSOR: M1.35 (P1.11/AIN4/CLK); also elsewhere on the board
MOTOR_IN1: M1.22 (P1.05/AIN1); also elsewhere on the board
MOTOR_IN2: M1.21 (P1.06/AIN2); also elsewhere on the board
unnamed: M1.25 (P1.00/XL1), X1.2 (out)
unnamed: M1.24 (P1.01/XL2), X1.1 (inp)
SCL: M1.17 (P0.00), R1.2; also elsewhere on the board
SDA: M1.18 (P0.01), R2.2; also elsewhere on the board
SWDCLK: M1.6 (SWDCLK); also elsewhere on the board
SWDIO: M1.5 (SWDIO); also elsewhere on the board
UNLOCKED_SENSOR: M1.34 (P1.12/AIN5/CLK); also elsewhere on the board
~CHG_PG: M1.20 (P1.07/AIN3); also elsewhere on the board
~RESET: M1.7 (NRESET); also elsewhere on the board

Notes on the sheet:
SoM:

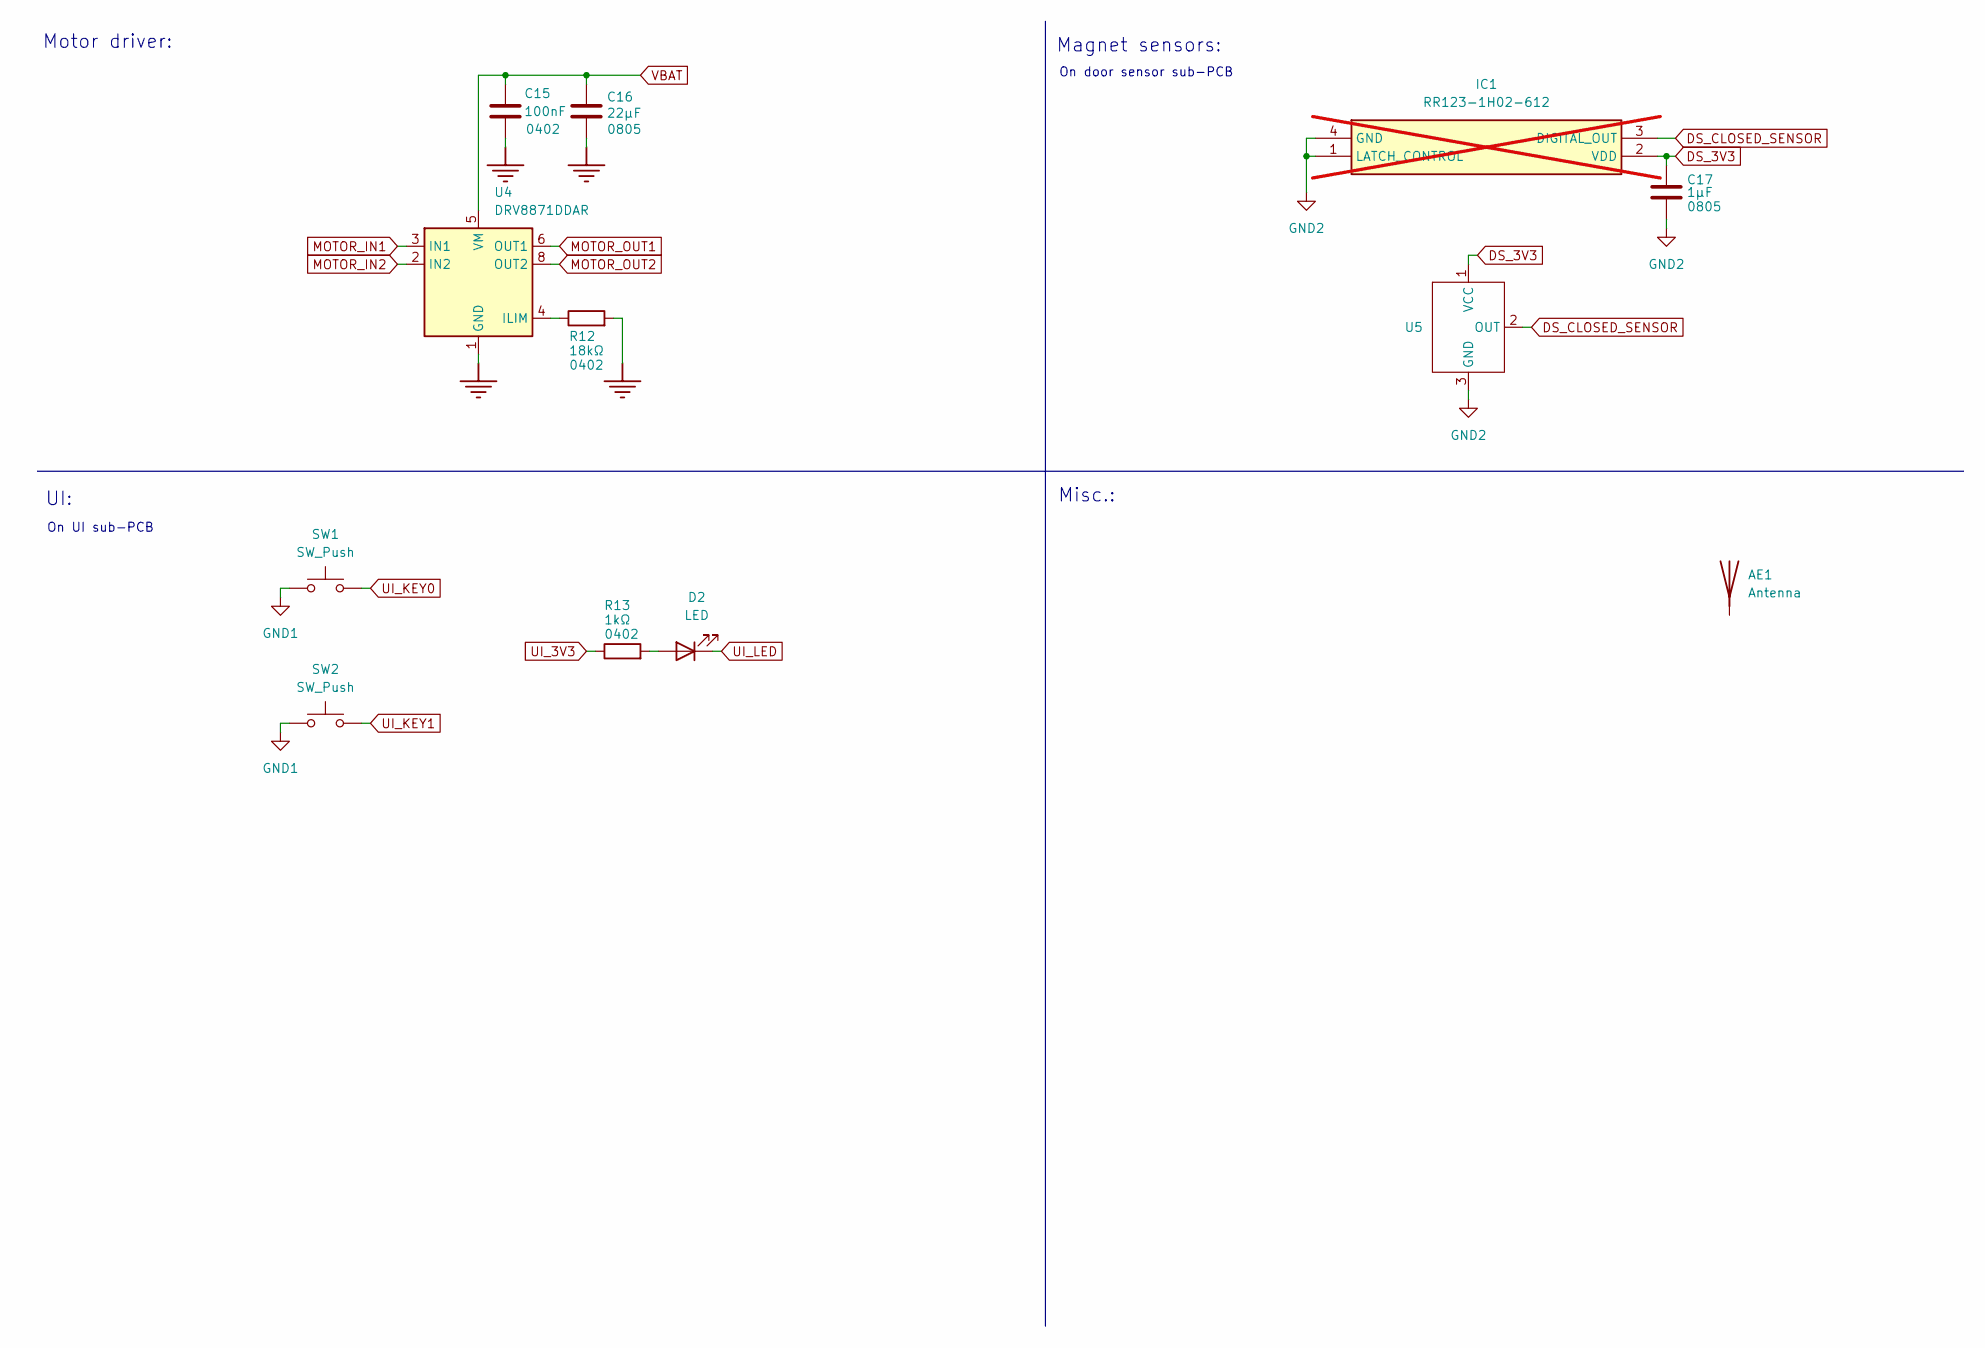
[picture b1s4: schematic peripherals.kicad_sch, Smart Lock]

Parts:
AE1: Antenna; MANUFACTURER PART NUMBER 2344656-6
C15: 100nF; C_0402_1005Metric; Voltage 16V; MANUFACTURER PART NUMBER GRM155R71C104KA88D
C16: 22µF; C_0805_2012Metric; Voltage 25V; MANUFACTURER PART NUMBER GRM21BR61E226ME44L
C17: 1µF; C_0805_2012Metric; Voltage 10V; MANUFACTURER PART NUMBER GRM21BR71A105KA01K
D2: LED; LED_0603_1608Metric; MANUFACTURER PART NUMBER TLMS1000-GS15
IC1: RR123-1H02-612; MANUFACTURER PART NUMBER RR123-1H02-612; not fitted
R12: 18kΩ; R_0402_1005Metric; MANUFACTURER PART NUMBER RC0402FR-0718KL
R13: 1kΩ; R_0402_1005Metric; MANUFACTURER PART NUMBER RC0402FR-071KL
SW1, SW2: SW_Push; SW_SPST_PTS647_Sx70; MANUFACTURER PART NUMBER PTS647SK70SMTR2 LFS
U4: DRV8871DDAR; HSOP-8-1EP_3.9x4.9mm_P1.27mm_EP2.41x3.1mm; MANUFACTURER PART NUMBER DRV8871DDAR
U5: SOT-23; MANUFACTURER PART NUMBER SL353LT

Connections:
DS_3V3: C17.1, IC1.2 (VDD), U5.1 (VCC); also elsewhere on the board
DS_CLOSED_SENSOR: IC1.3 (DIGITAL_OUT), U5.2 (OUT); also elsewhere on the board
GND: C15.2, C16.2, R12.2, U4.1 (GND), U4.7 (GND), U4.9 (GND); also elsewhere on the board
GND1: SW1.1, SW2.1; also elsewhere on the board
GND2: C17.2, IC1.1 (LATCH_CONTROL), IC1.4 (GND), U5.3 (GND); also elsewhere on the board
MOTOR_IN1: U4.3 (IN1); also elsewhere on the board
MOTOR_IN2: U4.2 (IN2); also elsewhere on the board
MOTOR_OUT1: U4.6 (OUT1); also elsewhere on the board
MOTOR_OUT2: U4.8 (OUT2); also elsewhere on the board
unnamed: D2.2 (A), R13.2
unnamed: R12.1, U4.4 (ILIM)
UI_3V3: R13.1; also elsewhere on the board
UI_KEY0: SW1.2; also elsewhere on the board
UI_KEY1: SW2.2; also elsewhere on the board
UI_LED: D2.1 (K); also elsewhere on the board
VBAT: C15.1, C16.1, U4.5 (VM); also elsewhere on the board

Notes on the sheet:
UI:
Misc.:
On UI sub-PCB
Magnet sensors:
Motor driver:
On door sensor sub-PCB

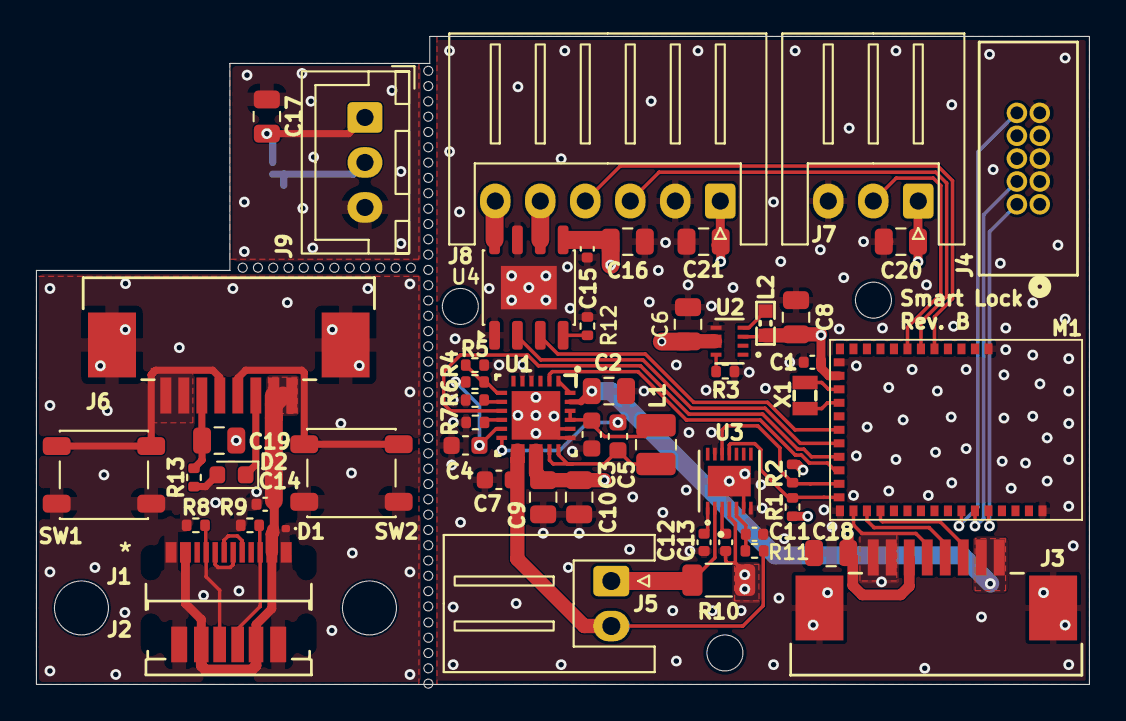
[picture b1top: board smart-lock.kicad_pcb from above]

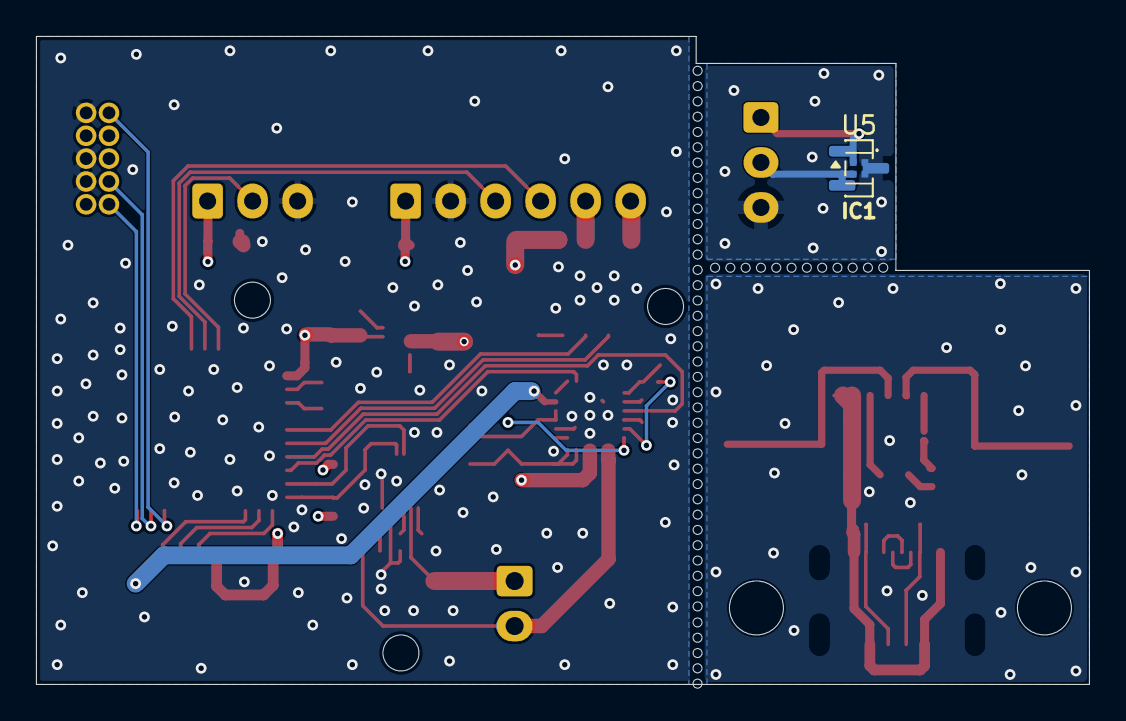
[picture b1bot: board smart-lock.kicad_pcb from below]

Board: 4 copper layers, 58.5 x 36.0 mm, 57 parts (2 on the bottom side), 53 nets.

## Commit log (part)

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2026-03-21 Initial empty commit

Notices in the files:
README.md:
License:
MIT - see [LICENSE](LICENSE).
Files under `boards/shmuelzon/lowkey/` derive from nRF Connect SDK board
templates and remain Apache-2.0, as marked in their headers.
